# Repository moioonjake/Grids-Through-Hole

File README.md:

# Grids Through-Hole aka Ruudukko

Grids through-hole is a through-hole adaptation of the Mutable Instruments Grids Topographic drum sequencer. It’s a 100% non-commercial effort developed purely for own educational purposes where I’m trying to learn to understand schematics, Kicad and PCB making.

As recommended I have changed the name on the PCB's, "Ruudukko" means Grids in Finnish.

Please note that this is not yet tested or verified (2020-05), I’d like to hear your feedback if you built this module so I can improve these files.

# Design
The original SMD PCB is all-in-one but since there's no space for THT components and keep the original control layout (Control board) I added secondary PCB for the "Brains" (Brains board). Basically this can be built without the Control board if you use wires from Brains board (from PINS(1-3).1 outputs) to output jacks, switch and potentiometers. Note that there's couple resistors and leds on the Control board so without the Control board add these to the jacks and switches.
<br><br>I also added those two bonus outs (clock and random gates) to the Control board upper right corner, these are optional like in the original. Also wire connect points to MIDI is moved to the Brains board, this requires wires to MIDI connector or add stereo 3.5mm jack and wire MIDI from Brains board to that.
<br><br>PCB's were made in Kicad and in the same board file and then separated.

Brains board:<br>
width : 74.93 mm<br>
height : 78.11 mm

Control board:<br>
width : 78.08 mm<br>
height : 102.87 mm

I'm going to do second Control board with thonkiconn jacks and board height under 100mm. The minus side on that is the original layout will be lost so with that Control board the original panel is not matching anymore and that board require different panel. So if you're going to make own panel then it does not matter.

Schematic is original, but I added two bonus outputs and resistors (v1.2), I did not add PINS(1-3).(1-2) to the schematic, only to the boards.

# Version History
v1.2
- Added resistors to two bonus outputs
  - Schema update
  - Control PCB update
  
v1.1
- Original release

# Panel
Original should work fine as the Control board layout as kept as original, if you want to use the bonus outs drill two holes to the panel upper right corner for jacks.

Link to the original panel files: https://github.com/pichenettes/eurorack/tree/master/grids/hardware_design/panel

# Possible updates
- Add: MIDI output to stereo 3.5mm jack to Control board. On the PINS3.(1-2) GND can be changed so that MIDI would be transported via PINS3.(1-2) pin6 between boards. Add stereo 3.5mm jack to Control board and wire TIP to the PINS3.2 pin6 and on the Brains board wire MIDI RX to PINS3.1 pin6.

# Notes
Original files, code & BOM can be found here: https://github.com/pichenettes/eurorack/tree/master/grids
<br>Note that BOM needs convert from SMD to THT components.

# License
Hardware: cc-by-sa-3.0

# Disclaimer of liability
The material and information contained on this website is for general information purposes only. You should not rely upon the material or information on the website as a basis for making any business, legal or any other decisions.
Whilst I endeavour to keep the information up to date and correct, I make no representations or warranties of any kind, express or implied about the completeness, accuracy, reliability, suitability or availability with respect to the website or the information, products, services or related graphics contained on the website for any purpose. Any reliance you place on such material is therefore strictly at your own risk.

I will not be liable for any false, inaccurate, inappropriate or incomplete information presented on the website.

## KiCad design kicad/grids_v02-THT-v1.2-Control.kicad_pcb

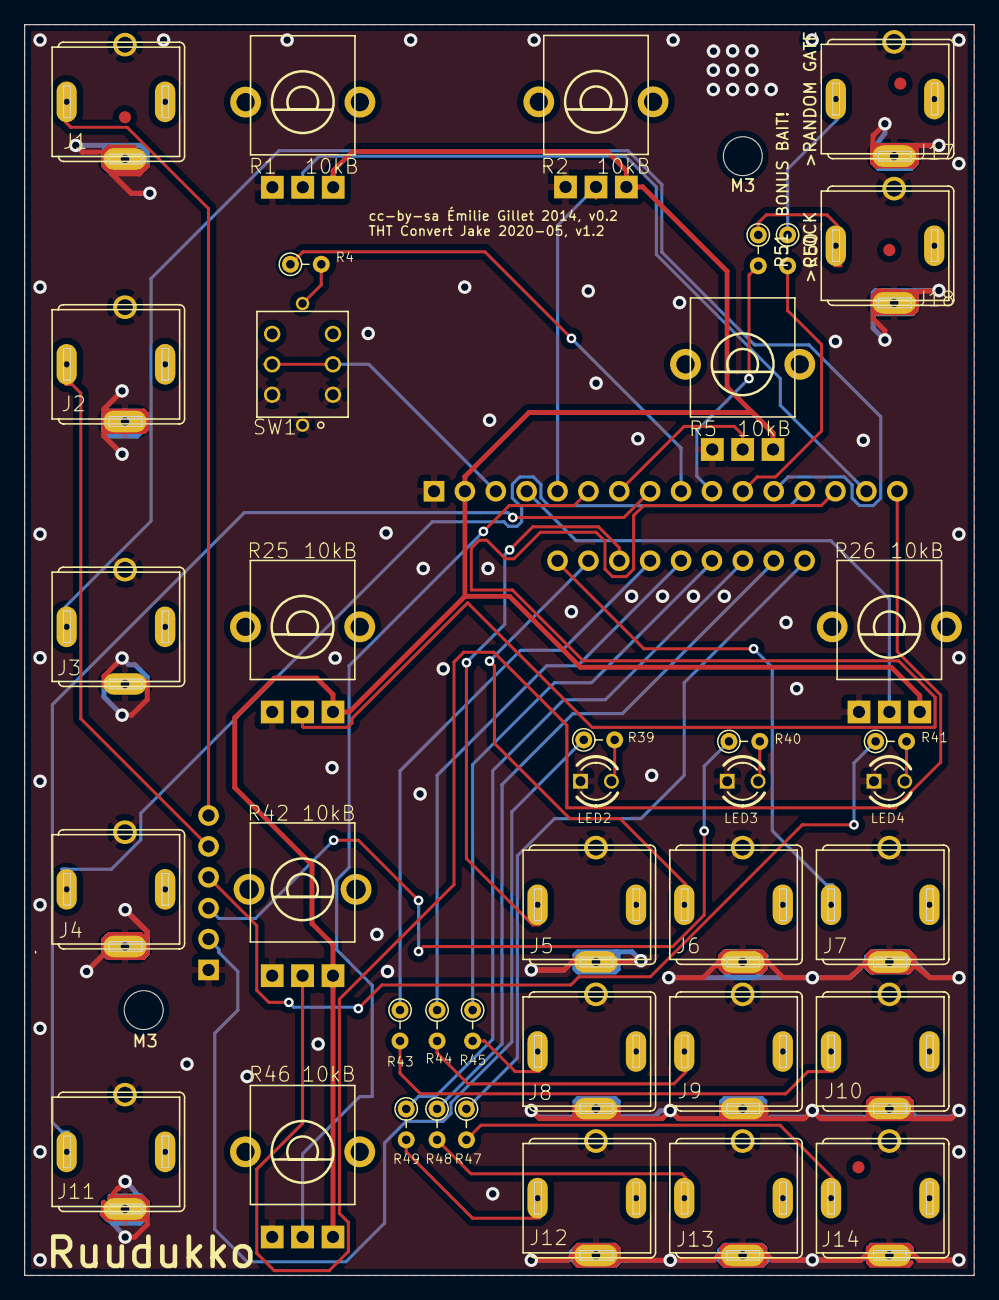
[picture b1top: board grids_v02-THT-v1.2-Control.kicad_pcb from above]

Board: 2 copper layers, 78.1 x 102.9 mm, 50 parts (0 on the bottom side), 42 nets.

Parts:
F1, F2, F3, F4: FIDUCIAL1X2; FIDUCIAL-1X2
J1, J2, J3, J4, J5, J6, J7, J8, J9, J10, J11, J12, J13, J14, J17, J18: PJ301WQP; WQP_PJ_301BM
LED2, LED3, LED4: LED3MM
M3, M3#2: MountingHole_3.2mm_M3
PINS1.2: PinHeader_1x16_P2.54mm_Vertical
PINS2.2: PinHeader_1x09_P2.54mm_Vertical
PINS3.2: PinHeader_1x06_P2.54mm_Vertical
R1, R2, R5, R25, R26, R46: 10kB; ALPS_POT_VERTICAL_PS
R4, R39, R40, R41: 100; R_Axial_DIN0204_L3.6mm_D1.6mm_P2.54mm_Vertical
R42: 10kB; ALPS_POT_VERTICAL_PS4
R43, R44, R45, R47, R48, R49, R50, R51: 1.0k; R_Axial_DIN0204_L3.6mm_D1.6mm_P2.54mm_Vertical
SW1: LP4OA1PBCT
U$1: EURORACK_TEMPLATE
U$2: ROHS_BIG

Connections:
+5V: PINS1.2.2, R1.P$1, R2.P$1, R5.P$1, R25.P$1, R26.P$1, R42.P$1, R46.P$1
/LED_CH1: PINS3.2.5, R39.1
/LED_CH2: PINS3.2.4, R40.1
/LED_CH3: PINS3.2.3, R41.1
/LED_CLOCK: PINS1.2.9, R4.1
/SW_RESET: PINS1.2.3, SW1.P2, SW1.P5
/TEMPO: PINS1.2.15, R1.P$2
GND: J1.GND, J1.GND2, J2.GND, J2.GND2, J3.GND, J3.GND2, J4.GND, J4.GND2, J5.GND, J5.GND2, J6.GND, J6.GND2, J7.GND, J7.GND2, J8.GND, J8.GND2, J9.GND, J9.GND2, J10.GND, J10.GND2, J11.GND, J11.GND2, J12.GND, J12.GND2, J13.GND, J13.GND2, J14.GND, J14.GND2, J17.GND, J17.GND2, J18.GND, J18.GND2, LED2.K, LED3.K, LED4.K, PINS1.2.1, PINS3.2.6, R1.P$3, R2.P$3, R5.P$3, R25.P$3, R26.P$3, R42.P$3, R46.P$3, SW1.L2, SW1.P3, SW1.P6
unnamed: PINS2.2.5, R44.1
unnamed: PINS2.2.4, R43.1
unnamed: PINS2.2.7, R49.1
unnamed: PINS2.2.8, R48.1
unnamed: PINS2.2.9, R47.1
unnamed: PINS1.2.10, R51.2
unnamed: PINS1.2.11, R50.2
unnamed: PINS2.2.6, R45.1
unnamed: J1.TIP, PINS3.2.1
unnamed: J2.TIP, PINS3.2.2
unnamed: J3.TIP, PINS1.2.12
unnamed: J4.TIP, PINS1.2.13
unnamed: J5.TIP, PINS2.2.3
unnamed: J6.TIP, PINS2.2.2
unnamed: J7.TIP, PINS2.2.1
unnamed: J8.TIP, R45.2
unnamed: J9.TIP, R44.2
unnamed: J10.TIP, R43.2
unnamed: J11.TIP, PINS1.2.8
unnamed: J12.TIP, R49.2
unnamed: J13.TIP, R48.2
unnamed: J14.TIP, R47.2
unnamed: J17.TIP, R50.1
unnamed: J18.TIP, R51.1
unnamed: LED2.A, R39.2
unnamed: LED3.A, R40.2
unnamed: LED4.A, R41.2
unnamed: R4.2, SW1.L1
unnamed: PINS1.2.16, R42.P$2
unnamed: PINS1.2.5, R2.P$2
unnamed: PINS1.2.4, R26.P$2
unnamed: PINS1.2.14, R25.P$2
unnamed: PINS1.2.6, R46.P$2
unnamed: PINS1.2.7, R5.P$2

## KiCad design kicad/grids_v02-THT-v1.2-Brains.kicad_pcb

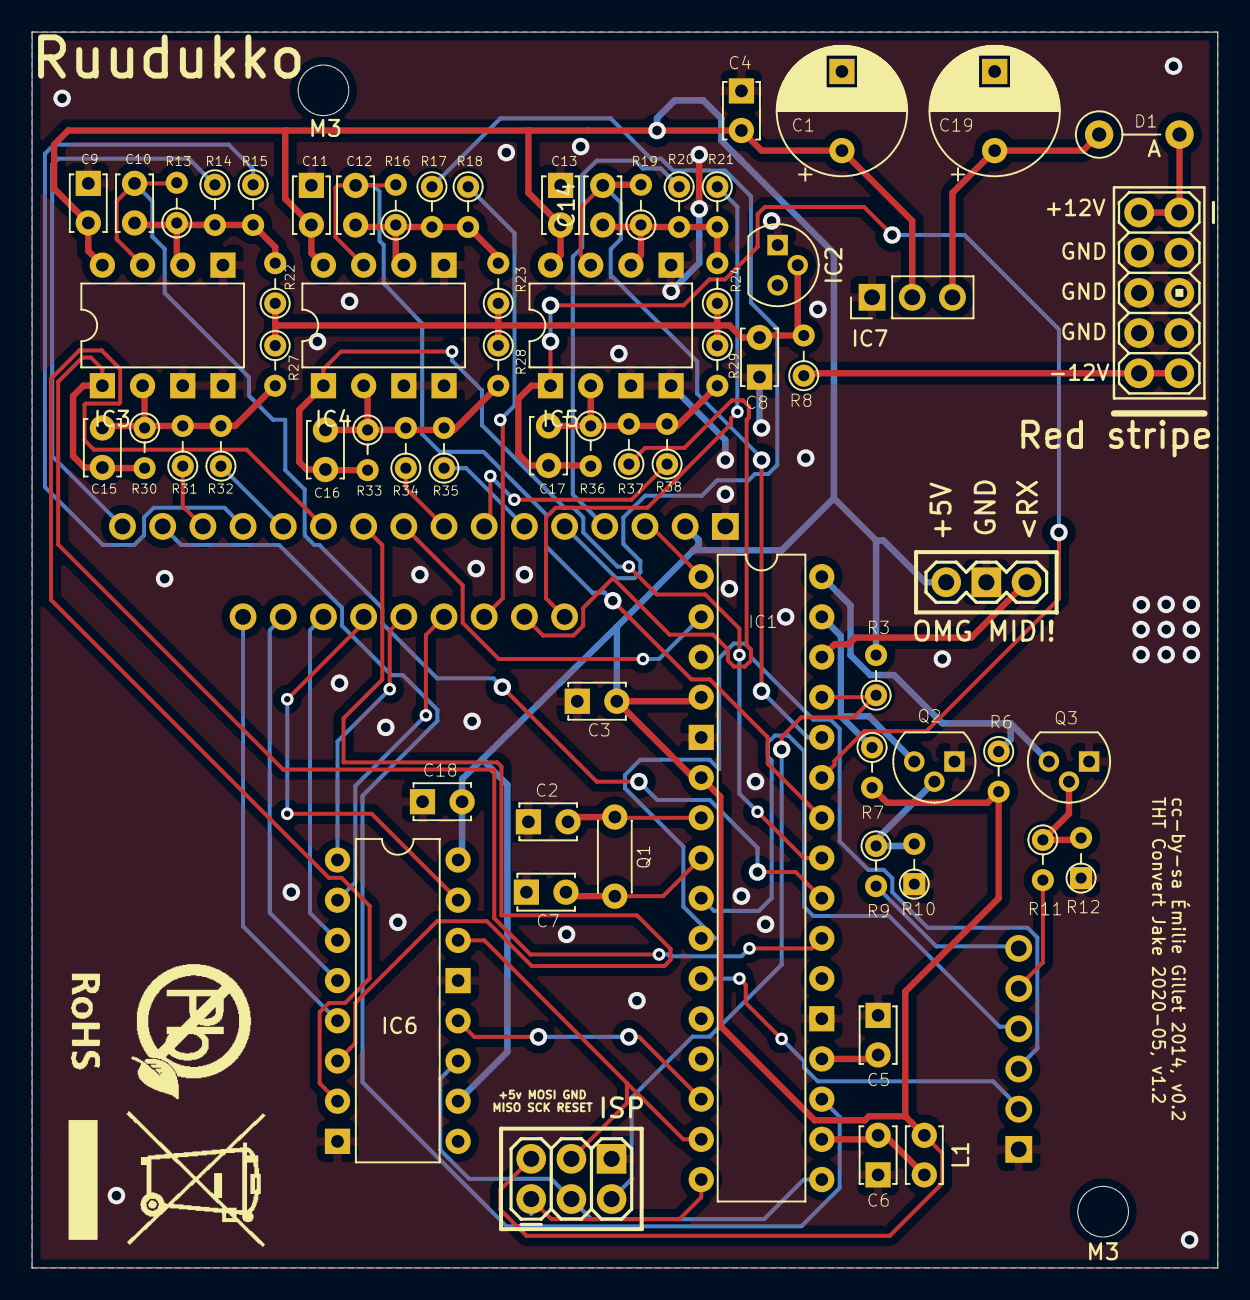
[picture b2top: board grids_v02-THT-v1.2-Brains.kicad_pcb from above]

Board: 2 copper layers, 74.9 x 78.1 mm, 73 parts (0 on the bottom side), 60 nets.

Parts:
C1, C19: 22u; CP_Radial_D8.0mm_P5.00mm
C2, C7: 18p; C_Disc_D3.4mm_W2.1mm_P2.50mm
C3, C4, C5, C6, C9, C11, C13, C18: 100n; C_Disc_D3.4mm_W2.1mm_P2.50mm
C8: 470n; C_Disc_D3.4mm_W2.1mm_P2.50mm
C10, C12, C14, C15, C16, C17: 10n; C_Disc_D3.4mm_W2.1mm_P2.50mm
D1: 1N5819HW; D_A-405_P5.08mm_Vertical_AnodeUp
IC1: ATMEGA328P-AU; DIP-32_W7.62mm
IC2: LM4040 5.0V; TO-92
IC3, IC4, IC5: MCP6002; DIP-8_W7.62mm
IC6: 74595D; DIP-16_W7.62mm
IC7: LM1117-5.0; PinHeader_1x03_P2.54mm_Vertical
J15: AVR_SPI_PRG_6PTH; 2X3
J16: M05X2PTH; AVR_ICSP
JP2: M03PTH; 1X03
L1: WE-CBF_0603; C_Disc_D3.4mm_W2.1mm_P2.50mm
M3, M3#2: MountingHole_3.2mm_M3
PINS1.1: PinHeader_1x16_P2.54mm_Vertical
PINS2.1: PinHeader_1x09_P2.54mm_Vertical
PINS3.1: PinHeader_1x06_P2.54mm_Vertical
Q1: 20MHz; C_Disc_D4.3mm_W1.9mm_P5.00mm
Q2, Q3: MMBT3904; TO-92
R3, R6, R7, R8: 10k; R_Axial_DIN0204_L3.6mm_D1.6mm_P2.54mm_Vertical
R9, R11, R13, R14, R15, R16, R17, R18, R19, R20, R21, R22, R23, R24, R27, R28, R29, R30, R31, R32, R33, R34, R35, R36, R37, R38: 100k; R_Axial_DIN0204_L3.6mm_D1.6mm_P2.54mm_Vertical
R10, R12: 1M; R_Axial_DIN0204_L3.6mm_D1.6mm_P2.54mm_Vertical
U$1: EURORACK_TEMPLATE
U$2: ROHS_BIG

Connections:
+5V: C1.1, C3.1, C4.1, C9.1, C11.1, C13.1, C18.1, IC1.4, IC1.6, IC3.8, IC4.8, IC5.8, IC6.10, IC6.16, IC7.2, J15.2, JP2.3, L1.1, PINS1.1.2, R3.2, R6.2, R7.2
/AREF: C5.1, IC1.20
/CH1_CV: C12.2, IC1.26, IC4.7, R16.2
/CH2_CV: C17.2, IC1.27, IC5.1, R36.2
/CH3_CV: C14.2, IC1.28, IC5.7, R19.2
/IN_CLOCK: IC1.31, Q2.C, R7.1
/IN_MIDI: IC1.30, JP2.1
/IN_RESET: IC1.32, Q3.C, R6.1
/LED_CH1: IC1.11, PINS3.1.5
/LED_CH2: IC1.10, PINS3.1.4
/LED_CH3: IC1.9, PINS3.1.3
/LED_CLOCK: IC1.2, PINS1.1.9
/MISO: IC1.16, J15.1
/MOSI: IC1.15, IC6.14, J15.4
/REF_-5: C8.1, IC2.2, R8.2, R22.1, R23.1, R24.1, R27.1, R28.1, R29.1
/RESET: IC1.29, J15.5, R3.1
/RND_CV: C16.2, IC1.25, IC4.1, R33.2
/SCK: IC1.17, IC6.11, J15.3
/SS: IC1.14, IC6.12
/SW_RESET: IC1.1, PINS1.1.3
/TEMPO: IC1.19, PINS1.1.15
/X_CV: C15.2, IC1.23, IC3.1, R30.2
/Y_CV: C10.2, IC1.24, IC3.7, R13.2
GND: C2.1, C3.2, C4.2, C5.2, C6.2, C7.1, C8.2, C9.2, C11.2, C13.2, C18.2, IC1.3, IC1.5, IC1.21, IC2.1, IC3.3, IC3.4, IC3.5, IC4.3, IC4.4, IC4.5, IC5.3, IC5.4, IC5.5, IC6.8, IC6.13, IC7.1, J15.6, J16.3, J16.4, J16.5, J16.6, J16.7, J16.8, JP2.2, PINS1.1.1, PINS3.1.6, Q2.E, Q3.E, R10.1, R12.1
unnamed: C2.2, IC1.7, Q1.2
unnamed: C6.1, IC1.18, L1.2
unnamed: C7.2, IC1.8, Q1.1
unnamed: C10.1, IC3.6, R13.1, R14.2, R15.2, R22.2
unnamed: C12.1, IC4.6, R16.1, R17.2, R18.2, R23.2
unnamed: C14.1, IC5.6, R19.1, R20.2, R21.2, R24.2
unnamed: C15.1, IC3.2, R27.2, R30.1, R31.2, R32.2
unnamed: C16.1, IC4.2, R28.2, R33.1, R34.2, R35.2
unnamed: C17.1, IC5.2, R29.2, R36.1, R37.2, R38.2
unnamed: D1.2, J16.9, J16.10
unnamed: IC6.1, PINS2.1.5
unnamed: IC6.2, PINS2.1.4
unnamed: IC6.3, PINS2.1.7
unnamed: IC6.4, PINS2.1.8
unnamed: IC6.5, PINS2.1.9
unnamed: IC6.6, PINS1.1.10
unnamed: IC6.7, PINS1.1.11
unnamed: IC6.15, PINS2.1.6
unnamed: PINS3.1.1, R9.2
unnamed: PINS3.1.2, R11.2
unnamed: PINS1.1.12, R32.1
unnamed: PINS1.1.13, R15.1
unnamed: PINS2.1.3, R18.1
unnamed: PINS2.1.2, R37.1
unnamed: PINS2.1.1, R21.1
unnamed: PINS1.1.8, R34.1
unnamed: Q2.B, R9.1, R10.2
unnamed: Q3.B, R11.1, R12.2
unnamed: PINS1.1.16, R14.1
unnamed: PINS1.1.5, R17.1
unnamed: PINS1.1.4, R20.1
unnamed: PINS1.1.14, R31.1
unnamed: PINS1.1.6, R35.1
unnamed: PINS1.1.7, R38.1
VCC: C19.1, D1.1, IC7.3
VEE: J16.1, J16.2, R8.1

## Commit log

2020-05-04 Rename grids_v02-THT-v1.1-Brains.kicad_pcb to kicad/grids_v02-THT-v1.1-Brains.kicad_pcb
2020-05-04 Rename grids_v02-THT-v1.1-Control.kicad_pcb to kicad/grids_v02-THT-v1.1-Control.kicad_pcb
2020-05-04 Rename grids_v02.sch to kicad/grids_v02.sch
2020-05-04 Create plop
2020-05-05 Rename grids_v02-THT-v1.2-Brains.kicad_pcb to kicad/grids_v02-THT-v1.2-Brains.kicad_pcb
2020-05-05 Rename grids_v02-THT-v1.2-Control.kicad_pcb to kicad/grids_v02-THT-v1.2-Control.kicad_pcb
2020-05-05 Rename grids_v02-THT-v1.2.sch to kicad/grids_v02-THT-v1.2.sch

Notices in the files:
kicad/grids_v02-THT-v1.2-Brains.kicad_pcb:
cc-by-sa Émilie Gillet 2014, v0.2
